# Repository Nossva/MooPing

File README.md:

<div align="center">
    
# [AgroNomad](https://linktr.ee/agronomad2026)

&nbsp;

| Página web | Email | Instagram | Tiktok |
|------------|-------|-----------|---------|
|[AgroNomad Page](https://agro-nomad-page.vercel.app)|nomadbusiness2026@gmail.com|[@proyecto.agronomad](https://www.instagram.com/proyecto.agronomad/)|[@proyecto.agronomad](https://www.tiktok.com/@proyecto.agronomad)|

### MONITOREO INTELIGENTE DE GANADO 

AgroNomad es un sistema de monitoreo inteligente de ganado que combina collares smart, sensores, posicionamiento GPS y comunicación LoRa para obtener información de los animales directamente desde el campo.

El sistema está compuesto por collares inteligentes, una estación de recepción fija y una interfaz de usuario que permite visualizar y gestionar la información obtenida.

---

## Objetivo

Desarrollar un sistema IoT que permita realizar el seguimiento remoto del ganado, obteniendo información sobre su ubicación, movimiento y diferentes parámetros del animal, y centralizando estos datos en una estación de control.

---

## Componentes del Proyecto  

### AgroNeck

Collar inteligente colocado en el animal.

Se encarga de adquirir y procesar la información proveniente de los sensores y transmitirla mediante LoRa hacia el AgroBot.

### AgroBot

Estación de recepción fija del sistema.

Recibe la información enviada por los AgroNeck y funciona como centro de control para los animales monitoreados.

### AgroServer

Interfaz de usuario del sistema.

Permite visualizar y gestionar la información recibida desde los AgroNeck a través del AgroBot.

---

## Estructura del Proyecto  
**docs/** Documentación e Informes del Proyecto  
**firmware/** Código de los Microcontroladores  
**hardware/** Esquemáticos y PCB  
**mechanical/** Diseños 3D  
**web/** Landing Page del Proyecto  

---

### AgroNeck  

### AgroBot

---

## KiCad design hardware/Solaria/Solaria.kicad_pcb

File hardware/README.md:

# hardware
Diseños electrónicos del ecosistema AgroNomad desarrollados en KiCad.

---

### Estructura del Proyecto
**AgroBot/** Estación de recepción fija con Raspberry Pi Zero 2W  
**Cortex/** Placa principal del AgroNeck con ESP32  
**LoraShield/** Módulo adaptador de Lora SMD a THT  
**MLXModule/** Placa de soporte del Sensor de Temperatura MLX90614  
**MOSFETAdapter/** Mini adaptador diseñado para convertir MOSFETs SMD a THT
**Solaria/** Placa de Alimentación Solar y Gestión Energética  

---

## AgroBot

## Cortex

## LoraShield

## MLXModule

## Solaria

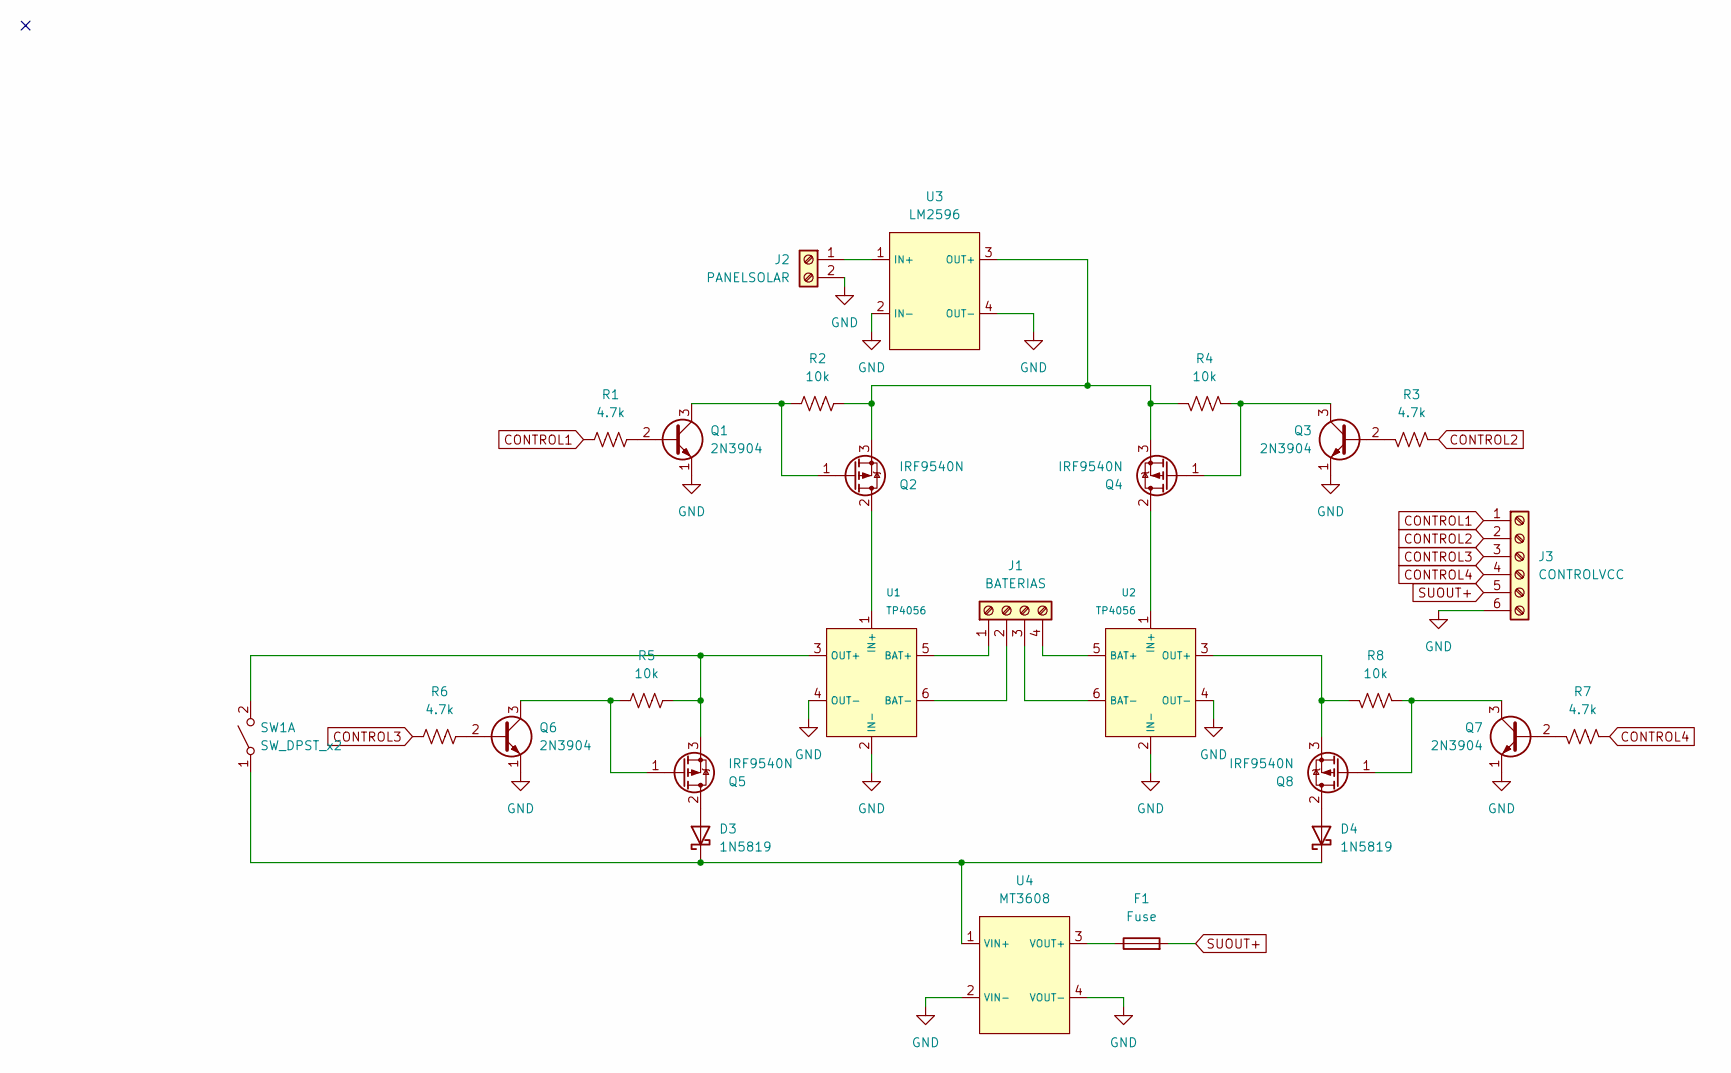
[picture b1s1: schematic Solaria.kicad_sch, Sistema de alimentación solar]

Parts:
D3, D4: 1N5819; D_DO-41_SOD81_P10.16mm_Horizontal
F1: Fuse; Fuseholder_Clip-5x20mm_Littelfuse_445-030_Inline_P20.50x5.2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
J1: BATERIAS; TerminalBlock_MaiXu_MX126-5.0-04P_1x04_P5.00mm
J2: PANELSOLAR; TerminalBlock_MaiXu_MX126-5.0-02P_1x02_P5.00mm
J3: CONTROLVCC; TerminalBlock_MaiXu_MX126-5.0-06P_1x06_P5.00mm
Q1, Q3, Q6, Q7: 2N3904; TO-92_Inline
Q2, Q4, Q5, Q8: IRF9540N; TO-220-3_Vertical
R1, R3, R6, R7: 4.7k; R_Axial_DIN0204_L3.6mm_D1.6mm_P7.62mm_Horizontal
R2, R4, R5, R8: 10k; R_Axial_DIN0204_L3.6mm_D1.6mm_P7.62mm_Horizontal
SW1: SW_DPST_x2; SW_PUSH-12mm_Wuerth-430476085716
U1, U2: TP4056
U3: LM2596
U4: MT3608

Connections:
CONTROL1: J3.1, R1.1
CONTROL2: J3.2, R3.1
CONTROL3: J3.3, R6.1
CONTROL4: J3.4, R7.1
GND: J2.2, J3.6, Q1.1 (E), Q3.1 (E), Q6.1 (E), Q7.1 (E), U1.2 (IN-), U1.4 (OUT-), U2.2 (IN-), U2.4 (OUT-), U3.2 (IN-), U3.4 (OUT-), U4.2 (VIN-), U4.4 (VOUT-)
unnamed: D3.2 (A), Q5.2 (D)
unnamed: D3.1 (K), D4.1 (K), SW1.1 (A), U4.1 (VIN+)
unnamed: D4.2 (A), Q8.2 (D)
unnamed: J1.1, U1.5 (BAT+)
unnamed: J1.2, U1.6 (BAT-)
unnamed: J1.3, U2.6 (BAT-)
unnamed: J1.4, U2.5 (BAT+)
unnamed: J2.1, U3.1 (IN+)
unnamed: Q1.2 (B), R1.2
unnamed: Q1.3 (C), Q2.1 (G), R2.1
unnamed: Q2.2 (D), U1.1 (IN+)
unnamed: Q2.3 (S), Q4.3 (S), R2.2, R4.2, U3.3 (OUT+)
unnamed: Q3.2 (B), R3.2
unnamed: Q3.3 (C), Q4.1 (G), R4.1
unnamed: Q4.2 (D), U2.1 (IN+)
unnamed: Q5.1 (G), Q6.3 (C), R5.1
unnamed: Q5.3 (S), R5.2, SW1.2 (B), U1.3 (OUT+)
unnamed: Q6.2 (B), R6.2
unnamed: Q7.2 (B), R7.2
unnamed: Q7.3 (C), Q8.1 (G), R8.1
unnamed: Q8.3 (S), R8.2, U2.3 (OUT+)
unnamed: F1.1, U4.3 (VOUT+)
SUOUT+: F1.2, J3.5

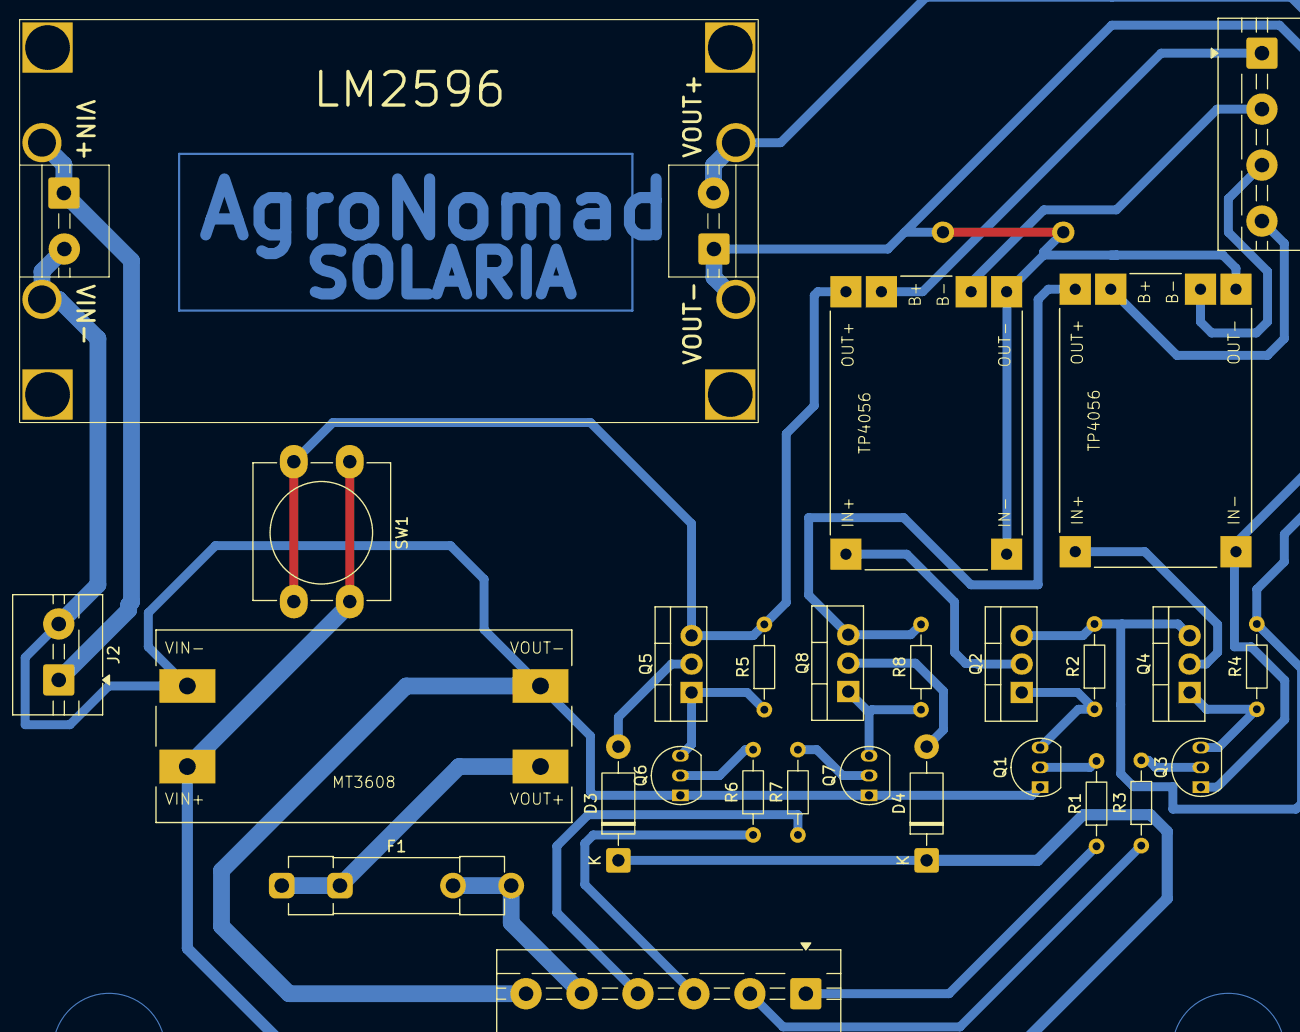
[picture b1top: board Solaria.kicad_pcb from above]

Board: 2 copper layers, 27 parts (0 on the bottom side), 28 nets.

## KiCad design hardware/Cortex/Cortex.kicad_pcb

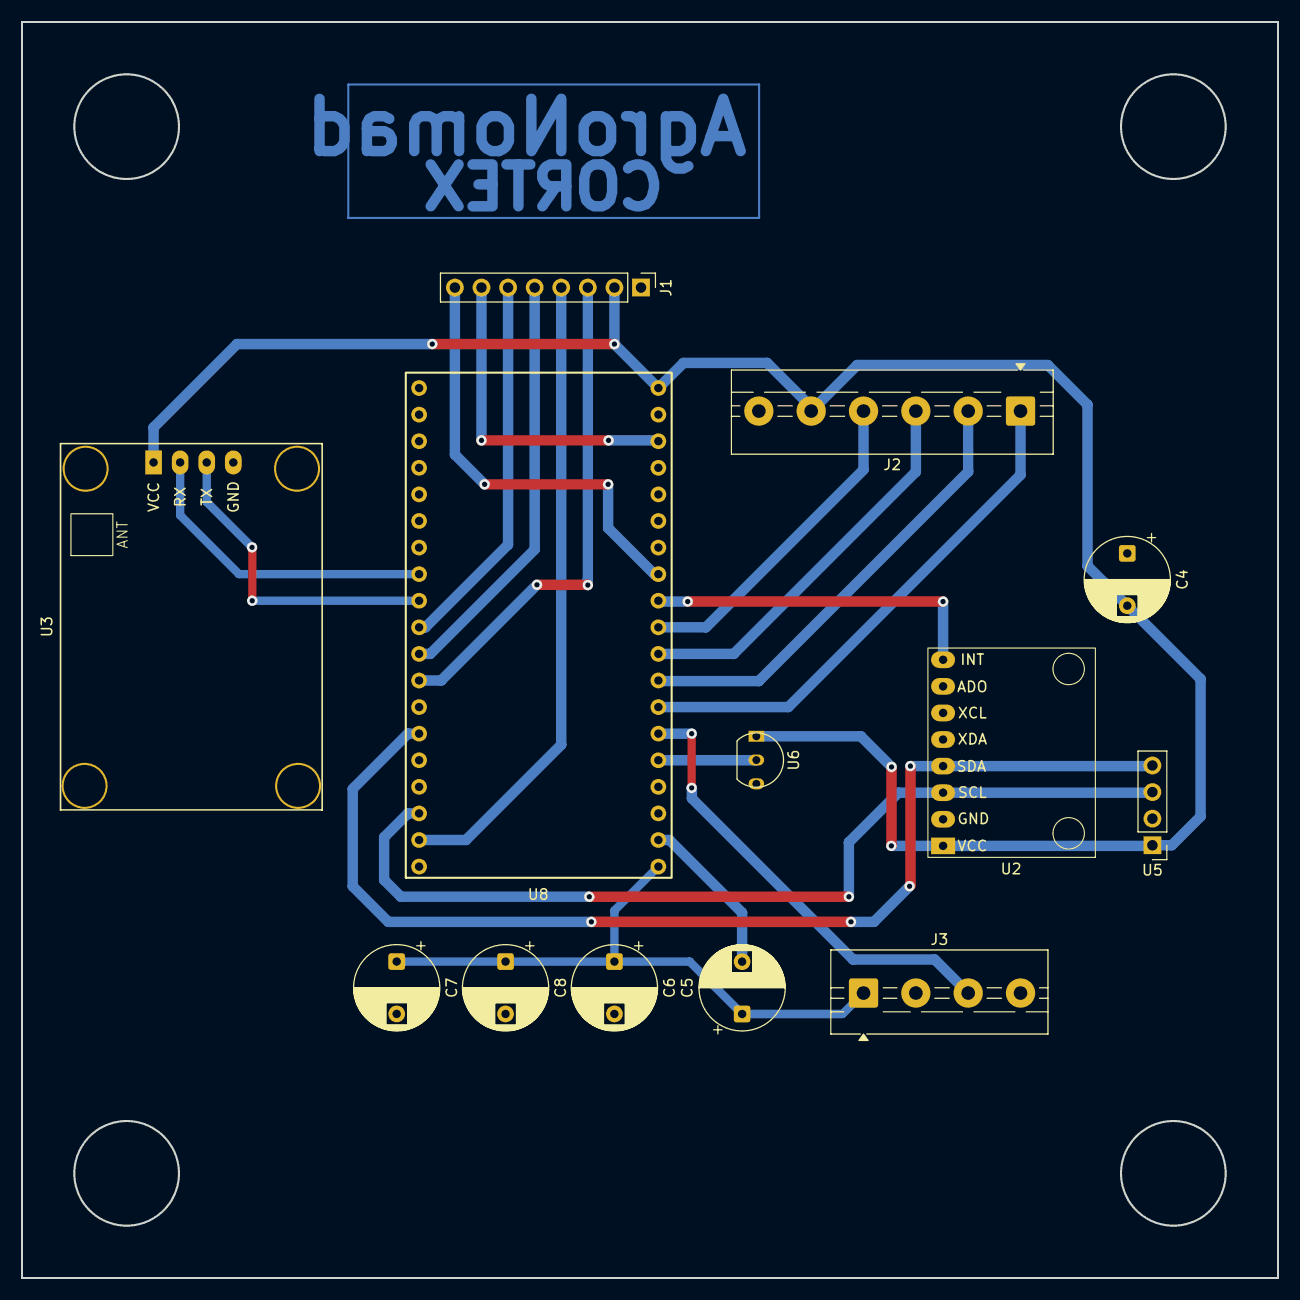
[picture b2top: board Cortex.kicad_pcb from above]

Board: 2 copper layers, 120.0 x 120.0 mm, 13 parts (0 on the bottom side), 21 nets.

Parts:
C4, C6: 100uF; CP_Radial_D8.0mm_P5.00mm
C5: 1uF; CP_Radial_D8.0mm_P5.00mm
C7: 0.1uF; CP_Radial_D8.0mm_P5.00mm
C8: 470uF; CP_Radial_D8.0mm_P5.00mm
J1: LoRa; PinHeader_1x08_P2.54mm_Vertical
J2: CONTROLVCC; TerminalBlock_MaiXu_MX126-5.0-06P_1x06_P5.00mm
J3: PIEZOELECTRICO; TerminalBlock_MaiXu_MX126-5.0-04P_1x04_P5.00mm
U2: MPU6050
U3: GY-NEO6MV2
U5: MLX90614; PinHeader_1x04_P2.54mm_Vertical
U6: LM35-LP; TO-92_Inline
U8: ESP32_devkit1

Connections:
+3V3: C5.1, C6.1, C7.1, C8.1, J3.1, U8.1 (3.3V)
CONTROL1: J2.1, U8.7 (GPIO32)
CONTROL2: J2.2, U8.8 (GPIO33)
CONTROL3: J2.3, U8.9 (GPIO25)
CONTROL4: J2.4, U8.10 (GPIO26)
GND: C4.1, C6.2, C7.2, C8.2, J1.1, J2.6, J3.2, J3.4, U2.2 (GND), U3.4 (GND), U5.2 (GND), U6.3 (GND), U8.14 (GND), U8.20 (GND), U8.26 (GND)
LORA_CLK: J1.5, U8.28 (GPIO18)
LORA_CS: J1.6, U8.29 (GPIO5)
LORA_DIO0: J1.7, U8.17 (GPIO13)
LORA_MISO: J1.3, U8.27 (GPIO19)
LORA_MOSI: J1.4, U8.21 (GPIO23)
LORA_RESET: J1.8, U8.12 (GPIO14)
MLX_MPU6050_SCL: U2.3 (SCL), U5.3 (SCL), U8.22 (GPIO22)
MLX_MPU6050_SDA: U2.4 (SDA), U5.4 (SDA), U8.25 (GPIO21)
MPU6050_INT: U2.8 (INT), U8.11 (GPIO27)
NEO6M_RX: U3.2 (RX), U8.31 (GPIO16)
NEO6M_TX: U3.3 (TX), U8.30 (GPIO17)
unnamed: C5.2, U8.2 (EN)
PIEZOELECTRICO_OUT: J3.3, U8.6 (GPIO35)
VCC: C4.2, J1.2, J2.5, U2.1 (VCC), U3.1 (VCC), U5.1 (VIN), U6.1 (+V_{S}), U8.19 (VIN)
V_LM35: U6.2 (V_{OUT}), U8.5 (GPIO34)

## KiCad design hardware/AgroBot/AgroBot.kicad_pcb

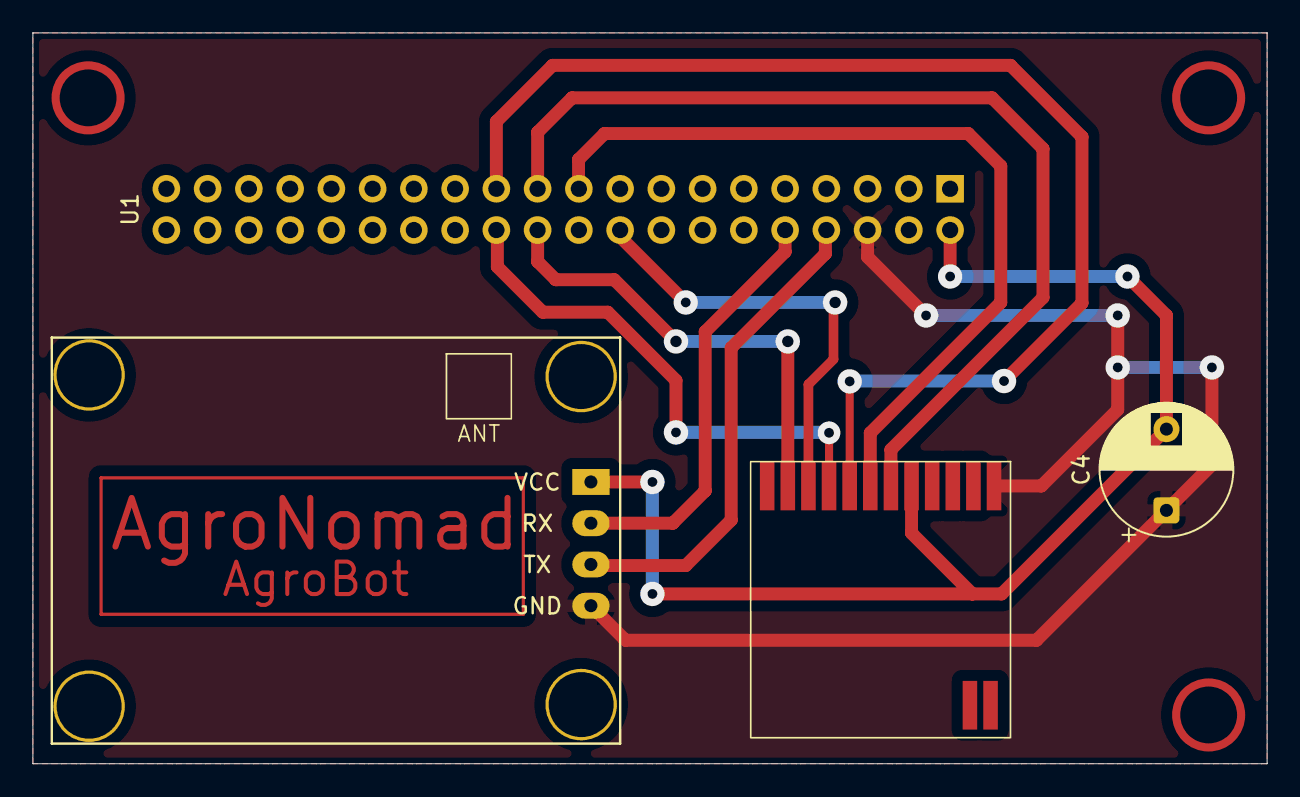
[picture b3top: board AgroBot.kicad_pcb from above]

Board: 2 copper layers, 76.0 x 45.0 mm, 4 parts (0 on the bottom side), 10 nets.

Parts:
C4: 100uF; CP_Radial_D8.0mm_P5.00mm
U1: Pi Zero 2 W; PinHeader_2x20_P2.54mm_Vertical
U2: XL1278
U3: GY-NEO6MV2

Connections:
GND: C4.1, U1.6 (GND), U2.1 (GND), U3.4 (GND)
GPS_RX: U1.10 (GPIO15), U3.2 (RX)
GPS_TX: U1.8 (GPIO14), U3.3 (TX)
LORA_CLK: U1.23 (GPIO11), U2.8 (SCLK)
LORA_CS: U1.24 (GPIO8), U2.9 (NSS)
LORA_DIO0: U1.18 (GPIO24), U2.10 (DIO0)
LORA_MISO: U1.21 (GPIO09), U2.6 (MISO)
LORA_MOSI: U1.19 (GPIO10), U2.7 (MOSI)
LORA_RESET: U1.22 (GPIO25), U2.11 (REST)
VCC: C4.2, U1.2 (+5V), U2.5 (VCC), U3.1 (VCC)

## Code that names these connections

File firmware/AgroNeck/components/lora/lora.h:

#include <stdint.h>

// Pines LORA
#define LORA_CS         5
#define LORA_RESET      14
#define LORA_CLK        18
#define LORA_MISO       19
#define LORA_MOSI       23
#define LORA_DIO0       10

// Estructuras
typedef struct __attribute__((packed)) {
    uint16_t id_collar;
    float temperatura;     
    int32_t latitud;       
    int32_t longitud;     
} payload_t;               

// Funciones
void lora_init(void);
void transmitir_datos(payload_t *paquete);

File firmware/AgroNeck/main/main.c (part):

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#define WAKEUP_LEVEL    1  // Activarse con nivel alto/flanco ascendente

// CONTROL DE ALIMENTACIÓN - C1+C4 o C2+C3
#define MOSFET1 25 // GPIO del MOSFET CONTROL3
#define MOSFET2 26 // GPIO del MOSFET CONTROL4
#define MOSFET3 32 // GPIO del MOSFET CONTROL1
#define MOSFET4 33 // GPIO del MOSFET CONTROL2

// Mascara de manejo de los 4 pines
#define GPIO_MOSFET_MASK ((1ULL<<MOSFET1) | (1ULL<<MOSFET2) | (1ULL<<MOSFET3) | (1ULL<<MOSFET4))
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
